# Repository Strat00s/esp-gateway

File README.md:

# esp-gateway
All-in-One ESP32 gateway.

### TODOs
LBT

work out repeated send (lost ok response)

save data on gateway

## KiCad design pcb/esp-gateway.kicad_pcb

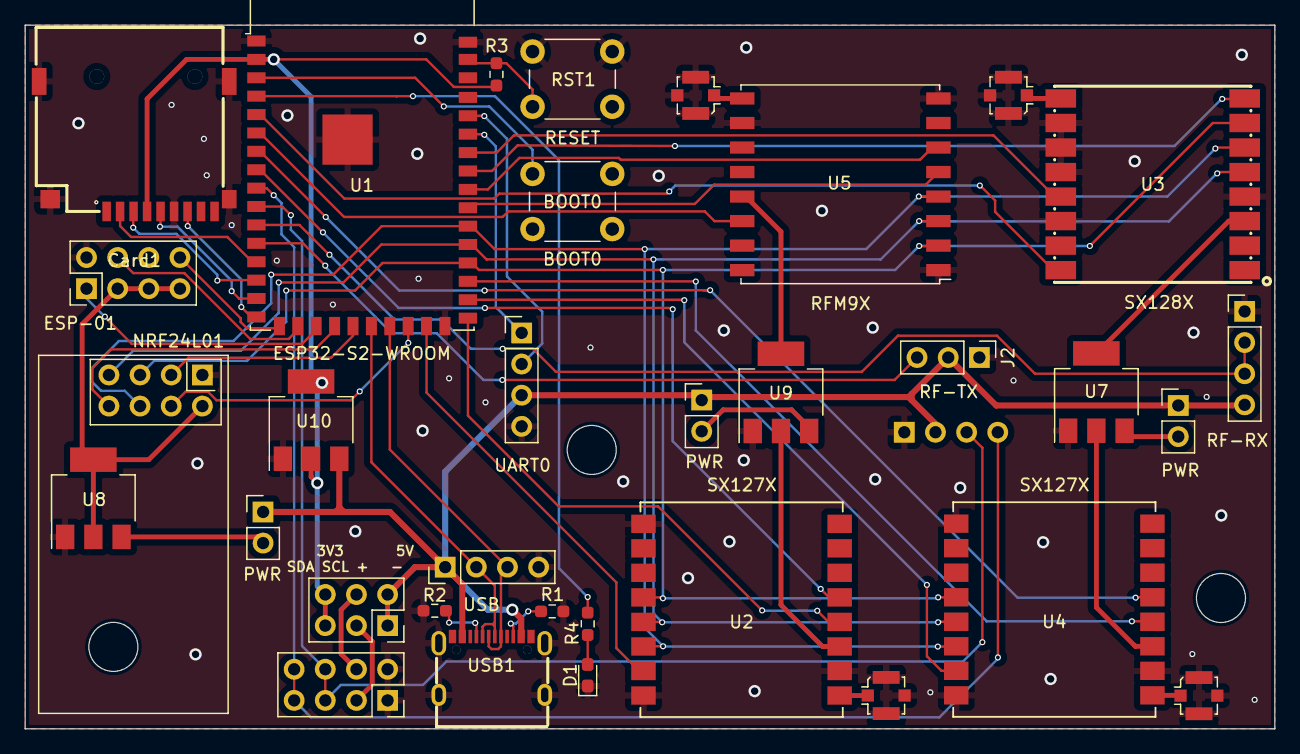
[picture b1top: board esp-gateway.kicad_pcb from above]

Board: 2 copper layers, 101.9 x 57.4 mm, 33 parts (0 on the bottom side), 54 nets.

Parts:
AE1, AE2, AE3, AE4: Antenna_Shield; U.FL_Molex_MCRF_73412-0110_Vertical
BOOT0: SW_PUSH_6mm
Card1: TF PUSH; TF-SMD_TF-PUSH
D1: RED; LED_0603_1608Metric_Pad1.05x0.95mm_HandSolder
J1: ESP-01; PinHeader_2x04_P2.54mm_Vertical
J2: RF-TR; PinHeader_1x03_P2.54mm_Vertical
J3: RF-RX; PinHeader_1x04_P2.54mm_Vertical
J4: USB; PinHeader_1x04_P2.54mm_Vertical
J5, J6, J8: Conn_01x02; PinHeader_1x02_P2.54mm_Vertical
J7: UART0; PinHeader_1x04_P2.54mm_Vertical
J9: Conn_02x04_Counter_Clockwise; PinSocket_2x04_P2.54mm_Vertical
J10: JMP; PinSocket_2x03_P2.54mm_Vertical
R1, R2: 5.11K; R_0603_1608Metric_Pad0.98x0.95mm_HandSolder
R3: 10K; R_0603_1608Metric_Pad0.98x0.95mm_HandSolder
R4: 330; R_0603_1608Metric_Pad0.98x0.95mm_HandSolder
RST1: SW_PUSH_6mm
U1: ESP32-S2-WROVER
U2, U4: Ai-Thinker-Ra-01; Ai-Thinker-Ra-01-LoRa
U3: LORA1281-2.4GHZ; COMM-SMD_LORA1281-2.4GHZ
U5: RFM95W-868S2; HOPERF_RFM9XW_SMD
U6: NRF24L01_Breakout; nRF24L01_Breakout
U7, U8, U9, U10: AMS1117-3.3; SOT-223-3_TabPin2
USB1: TYPE-C 16PIN 2MD(073); USB-C-SMD_TYPE-C-6PIN-2MD-073

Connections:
3V3_ESP: Card1.4 (VDD), J10.5, J10.6, R3.1, U1.2 (3V3), U10.2 (VO)
3V3_NRF/01: J1.3, J1.5, J1.7, U6.2 (VCC), U8.2 (VO)
3V3_P1: U2.3 (VDD), U5.13 (3.3V), U9.2 (VO)
3V3_P2: U3.3 (VCC), U4.3 (VDD), U7.2 (VO)
+5V: J2.2, J3.4, J4.1, J5.1, J6.1, J7.3, J8.1, J10.1, J10.2, U10.3 (VI), USB1.2 (VBUS), USB1.11 (VBUS)
/01_IRQ: J1.4, U1.18 (IO15)
/DIO0-1: U1.8 (IO05), U2.5 (DIO0)
/DIO0-2: U1.7 (IO04), U4.5 (DIO0)
/DIO0-3: U1.5 (IO02), U3.16 (DIO1)
/DIO0-4: U1.6 (IO03), U5.14 (DIO0)
/FMISO: Card1.7 (DAT0), U1.16 (IO13)
/FMOSI: Card1.3 (CMD), U1.14 (IO11)
/FSCK: Card1.5 (CLX), U1.15 (IO12)
/MISO: U1.31 (IO37), U2.13 (MISO), U3.5 (MISO), U4.13 (MISO), U5.3 (MOSI), U6.7 (MISO)
/MOSI: U1.32 (IO38), U2.14 (MOSI), U3.6 (MOSI), U4.14 (MOSI), U5.4 (SCK), U6.6 (MOSI)
/NRF_CE: U1.21 (IO18), U6.3 (CE)
/NRF_CS: U1.24 (IO21), U6.4 (~CSN)
/NRF_IRQ: U1.20 (IO17), U6.8 (IRQ)
/NSS1: U1.25 (IO26), U2.15 (~NSS)
/NSS2: U1.28 (IO34), U4.15 (~NSS)
/NSS3: U1.35 (IO41), U3.8 (NSS)
/NSS4: U1.33 (IO39), U5.5 (NSS)
/RF_IN: J2.3, U1.12 (IO09)
/RF_OUT: J3.2, J3.3, U1.11 (IO08)
/RST1: U1.27 (IO33), U2.4 (~RESET)
/RST2: U1.29 (IO35), U4.4 (~RESET)
/RST3: U1.36 (IO42), U3.13 (NRESET)
/RST4: U1.34 (IO40), U5.6 (RESET)
/RX0: J7.2, U1.38 (RXD0)
/RX1: J1.1, U1.19 (IO16)
/SCK: U1.30 (IO36), U2.12 (SCK), U3.7 (SCK), U4.12 (SCK), U5.2 (MISO), U6.5 (SCK)
/SCL: J9.5, J9.6, U1.10 (IO07)
/SDA: J9.7, J9.8, U1.9 (IO06)
/SD_CS: Card1.2 (CD/DAT3), U1.13 (IO10)
/TX0: J7.1, U1.37 (TXD0)
/TX1: J1.8, U1.17 (IO14)
/USB_D+: J4.3, U1.23 (USB_D+), USB1.6 (DP1), USB1.8 (DP2)
/USB_D-: J4.2, U1.22 (USB_D-), USB1.5 (DN2), USB1.7 (DN1)
GND: AE1.2 (Shield), AE2.2 (Shield), AE3.2 (Shield), AE4.2 (Shield), BOOT0.1, Card1.6 (VSS), Card1.10, Card1.11, Card1.12, Card1.13, D1.1 (K), J1.2, J2.1, J3.1, J4.4, J7.4, J9.1, J9.2, R1.2, R2.1, RST1.1, U1.1 (GND), U1.26 (GND), U1.42 (GND), U1.43 (GND), U2.2 (GND), U2.9 (GND), U2.16 (GND), U3.4 (GND), U3.10 (GND), U3.11 (GND), U3.12 (GND), U3.14 (GND), U4.2 (GND), U4.9 (GND), U4.16 (GND), U5.1 (GND), U5.8 (GND), U5.10 (GND), U6.1 (GND), U7.1 (GND), U8.1 (GND), U9.1 (GND), U10.1 (GND), USB1.1 (GND), USB1.12 (GND), USB1.13 (SHELL), USB1.14 (SHELL)
unnamed: AE1.1 (A), U3.9 (ANT)
unnamed: AE2.1 (A), U2.1 (ANT)
unnamed: AE3.1 (A), U4.1 (ANT)
unnamed: AE4.1 (A), U5.9 (ANT)
unnamed: D1.2 (A), R4.1
unnamed: J5.2, U7.3 (VI)
unnamed: J6.2, U9.3 (VI)
unnamed: J8.2, U8.3 (VI)
unnamed: J9.3, J10.3
unnamed: J9.4, J10.4
unnamed: R3.2, RST1.2, U1.41 (EN)
unnamed: BOOT0.2, U1.3 (IO00)
unnamed: R4.2, U1.4 (IO01)
unnamed: R2.2, USB1.4 (CC1)
unnamed: R1.1, USB1.10 (CC2)

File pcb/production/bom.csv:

Designator,Footprint,Quantity,Value,LCSC Part #
"AE1, AE2, AE3, AE4",U.FL_Molex_MCRF_73412-0110_Vertical,4,Antenna_Shield,
"BOOT0, RST1",SW_PUSH_6mm,2,~,
Card1,TF-SMD_TF-PUSH,1,TF PUSH,C393941
D1,0603,1,RED,
J1,PinHeader_2x04_P2.54mm_Vertical,1,ESP-01,
J10,PinSocket_2x03_P2.54mm_Vertical,1,JMP,
J2,PinHeader_1x03_P2.54mm_Vertical,1,RF-TR,
J3,PinHeader_1x04_P2.54mm_Vertical,1,RF-RX,
J4,PinHeader_1x04_P2.54mm_Vertical,1,USB,
"J5, J6, J8",PinHeader_1x02_P2.54mm_Vertical,3,Conn_01x02,
J7,PinHeader_1x04_P2.54mm_Vertical,1,UART0,
J9,PinSocket_2x04_P2.54mm_Vertical,1,Conn_02x04_Counter_Clockwise,
"R1, R2",0603,2,5.11K,
R3,0603,1,10K,
R4,0603,1,330,
U1,ESP32-S2-WROVER,1,ESP32-S2-WROVER,
"U10, U7, U8, U9",SOT-223-3_TabPin2,4,AMS1117-3.3,
"U2, U4",Ai-Thinker-Ra-01-LoRa,2,Ai-Thinker-Ra-01,
U3,COMM-SMD_LORA1281-2.4GHZ,1,LORA1281-2.4GHZ,C3001531
U5,HOPERF_RFM9XW_SMD,1,RFM95W-868S2,
U6,nRF24L01_Breakout,1,NRF24L01_Breakout,
USB1,USB-C-SMD_TYPE-C-6PIN-2MD-073,1,TYPE-C 16PIN 2MD(073),C2765186

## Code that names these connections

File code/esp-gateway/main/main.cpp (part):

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#define MOSI GPIO_NUM_38
//lora modules
#define CS1   GPIO_NUM_26
#define RST1  GPIO_NUM_33
#define DIO01 GPIO_NUM_5
#define CS2   GPIO_NUM_34
#define RST2  GPIO_NUM_35
#define DIO02 GPIO_NUM_4
#define CS3   GPIO_NUM_41
#define RST3  GPIO_NUM_42
#define DIO03 GPIO_NUM_2
#define CS4   GPIO_NUM_39
#define RST4  GPIO_NUM_40
#define DIO04 GPIO_NUM_3
//NRF240L1+ module
#define NRF_IRQ GPIO_NUM_17
#define NRF_CE  GPIO_NUM_18
#define NRF_CS  GPIO_NUM_21
//ESP-01
#define TX1    GPIO_NUM_14
#define RX1    GPIO_NUM_16
#define IRG_01 GPIO_NUM_15
//434MHz rf modules
#define RF_IN  GPIO_NUM_9
#define RF_OUT GPIO_NUM_8
//SD card
#define SD_SCK  GPIO_NUM_12
#define SD_MISO GPIO_NUM_13
#define SD_MOSI GPIO_NUM_11
#define SD_CS   GPIO_NUM_10


#define DATA_LEN 16
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    gpio_reset_pin(MOSI);

    gpio_reset_pin(CS1);
    gpio_reset_pin(RST1);
    gpio_reset_pin(DIO01);
    gpio_reset_pin(CS2);
    gpio_reset_pin(RST2);
    gpio_reset_pin(DIO02);
    gpio_reset_pin(CS3);
    gpio_reset_pin(RST3);
    gpio_reset_pin(DIO03);
    gpio_reset_pin(CS4);
    gpio_reset_pin(RST4);
    gpio_reset_pin(DIO04);

    gpio_reset_pin(SDA);
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    
    gpio_reset_pin(STATUS_LED);

    gpio_reset_pin(NRF_IRQ);
    gpio_reset_pin(NRF_CE);
    gpio_reset_pin(NRF_CS);

    gpio_reset_pin(TX1);
    gpio_reset_pin(RX1);
    gpio_reset_pin(IRG_01);

    gpio_reset_pin(RF_IN);
    gpio_reset_pin(RF_OUT);
    
    gpio_reset_pin(SD_SCK);
    gpio_reset_pin(SD_CS);
    gpio_reset_pin(SD_MOSI);
    gpio_reset_pin(SD_MISO);

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
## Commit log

2023-07-19 pcb almost done
2023-07-20 done
2023-07-27 kikit tabs
2023-08-10 fix rfm pinout
2023-08-20 source start
2023-08-22 progress
2023-08-22 comments and descriptions
2023-08-22 spiMakeTranaction and read/write/set registers
2023-08-23 flags as single bit, register access
2023-08-24 working SPI read
2023-08-24 working spi functions (IT WORKS NOW!!!)
2023-08-25 working spi functions (IT WORKS AGAIN!!!)
2023-08-25 reset was the thing
2023-08-25 callbacks work
2023-08-30 almost done
2023-08-30 transmit and receive start
2023-08-31 errata
2023-08-31 basic receive and transfer done?
2023-08-31 working transmit and receive + simple main for receive
2023-08-31 non-blocking function (maybe it works)
2023-09-01 receive function rename
2023-09-01 continuous receive
2023-09-01 header setting
2023-09-01 changed reset delay to 10ms -> esp fix
2023-09-02 minor sx change, simple status led
2023-09-03 configure lora
2023-09-03 remove useless includes
2023-09-10 mqtt task
2023-09-14 mqtt basic structures
2023-11-03 protocol start
2023-11-07 length fix
2023-11-08 protocol idea
2023-11-10 protocol basics mostly done
2023-11-10 protocl renamed to tinymesh and total rework
2023-11-11 check mostly done
2023-11-11 rework mostly done
2023-11-12 allow software transmision finish detection
2023-11-12 some start, still a lot to do
2023-11-13 some basic handlers
2023-11-14 interface empty classes, lora434 interface class
2023-11-14 replace value with macro
2023-11-14 big rework (again)
2023-11-14 outgoin packet done, send on interface done
2023-11-14 fix destructor
2023-11-14 fix interfacewrapper define
2023-11-14 todo
2023-11-14 string.h instead of cstring, fix getMessageId()
2023-11-14 probably threadsafe deque
2023-11-14 threadsafe deque and on way to finishing handlers
2023-11-15 fix port definition macros
2023-11-15 todo return from transmitdata
2023-11-15 finish updateNode, fix handlepacket
2023-11-15 updateNode done
2023-11-16 minor changes
2023-11-16 another rework
2023-11-18 some rework done
2023-11-18 more rework
2023-11-21 CHECK_RET, checkpacket returns
2023-11-22 small updates
2023-11-22 simplify, make it work in small
2023-11-22 fix type in name
2023-11-23 simple register done
2023-11-23 fixed broadcast messages
2023-11-24 register somewhat works
2023-11-25 temporary error response codes
2023-11-25 create nodes and proper ids
2023-11-25 remove arduino library
2023-11-25 change sync workd on different lora devices
2023-11-25 rename lora interfaces to sx127x
2023-11-25 remove old lora wrapper
2023-11-26 tm update
2023-11-27 tm port rework
2023-11-27 tm rework
2023-11-27 another tinymesh update/rework
2023-11-27 small fix
2024-01-01 sx127x update
2024-01-02 another massive rewrite
2024-01-02 big rewrite hopefuly mostly done
2024-01-02 rewrite finished?
2024-01-02 replace binary semaphore with mutex
2024-01-02 working ping
2024-01-02 bigger factory space
2024-01-03 it works?
2024-01-03 basic cmd parsing
2024-01-03 mostly done
2024-01-03 mqtt next
2024-01-03 mqtt interface input
2024-01-03 basic custom telemetry (but not tested)
2024-01-03 minor not-a-fix
2024-01-04 last big rework for quite some time
2024-01-04 Todos in README.md
2024-01-17 fix save
2024-01-17 some fixes
2024-01-17 miner changes
2024-01-17 final changes
2024-01-18 wifi creds
2024-01-21 change to proper queue
2024-03-16 inteface rework
2024-03-20 big rework continued
2024-04-04 big rework almost done
2024-04-12 big rework ahead again
2024-04-16 another rework ahead for lbt
2024-04-17 something minor
2024-04-19 second big rework
2024-04-20 second big rework done
2024-05-25 add insert; not done yet
2024-05-25 rework continued
2024-05-26 fix typo
2024-05-26 working ping pong example
2024-05-26 templated data len
2024-05-27 big rework continued. Time on air and waiting for medium implemented?
2024-05-27 config update
2024-05-28 big rework almost done. It works in this statte.
2024-05-29 remove useless stuff
2024-05-31 fixed send_queued medium_busy oscilation
2024-06-02 keep responses for some time to resend; TODO: do it better
2024-06-02 fix where packet flag for response was set wrong
2024-06-02 remove delayed response test
